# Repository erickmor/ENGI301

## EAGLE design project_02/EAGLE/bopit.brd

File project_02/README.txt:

# --------------------------------------------------------------------------
# Bop It Project PCB
# --------------------------------------------------------------------------
# License:   
Copyright 2021 Erick Morales

Redistribution and use in source and binary forms, with or without 
modification, are permitted provided that the following conditions are met:
 
1. Redistributions of source code must retain the above copyright notice, this 
list of conditions and the following disclaimer.
 
2. Redistributions in binary form must reproduce the above copyright notice, 
this list of conditions and the following disclaimer in the documentation 
and/or other materials provided with the distribution.

3. Neither the name of the copyright holder nor the names of its contributors 
may be used to endorse or promote products derived from this software without 
specific prior written permission.
 
THIS SOFTWARE IS PROVIDED BY THE COPYRIGHT HOLDERS AND CONTRIBUTORS "AS IS" 
AND ANY EXPRESS OR IMPLIED WARRANTIES, INCLUDING, BUT NOT LIMITED TO, THE 
IMPLIED WARRANTIES OF MERCHANTABILITY AND FITNESS FOR A PARTICULAR PURPOSE ARE 
DISCLAIMED. IN NO EVENT SHALL THE COPYRIGHT HOLDER OR CONTRIBUTORS BE LIABLE 
FOR ANY DIRECT, INDIRECT, INCIDENTAL, SPECIAL, EXEMPLARY, OR CONSEQUENTIAL 
DAMAGES (INCLUDING, BUT NOT LIMITED TO, PROCUREMENT OF SUBSTITUTE GOODS OR 
SERVICES; LOSS OF USE, DATA, OR PROFITS; OR BUSINESS INTERRUPTION) HOWEVER 
CAUSED AND ON ANY THEORY OF LIABILITY, WHETHER IN CONTRACT, STRICT LIABILITY, 
OR TORT (INCLUDING NEGLIGENCE OR OTHERWISE) ARISING IN ANY WAY OUT OF THE USE 
OF THIS SOFTWARE, EVEN IF ADVISED OF THE POSSIBILITY OF SUCH DAMAGE.
--------------------------------------------------------------------------

Hello!

This is a homemade version of Bop It along with its PCB design and gbr files. 
gbr files can be opened using gerbv software. 
To manufacture, site that was referenced was macrofab. 
Software used to develop PCB Design was EAGLE.
Most components were provided by Erik Welsh.
LCD Display was downloaded from this Github Repository.
 - https://github.com/eez-open/eagle-libraries
Joystick and PocketBeagle symbol components was created by me.  
Folder includes Library used, Schematics, and Layout.
Manufacturing folder with all gbr files is also provided.
Bill of Materials is also included.
 
Please reference Hackster.io page (https://www.hackster.io/ejm9/pocketbeagle-bop-it-project-39caf6)
    for more information on this project.
Link to Guthub
    - https://github.com/erickmor/ENGI301

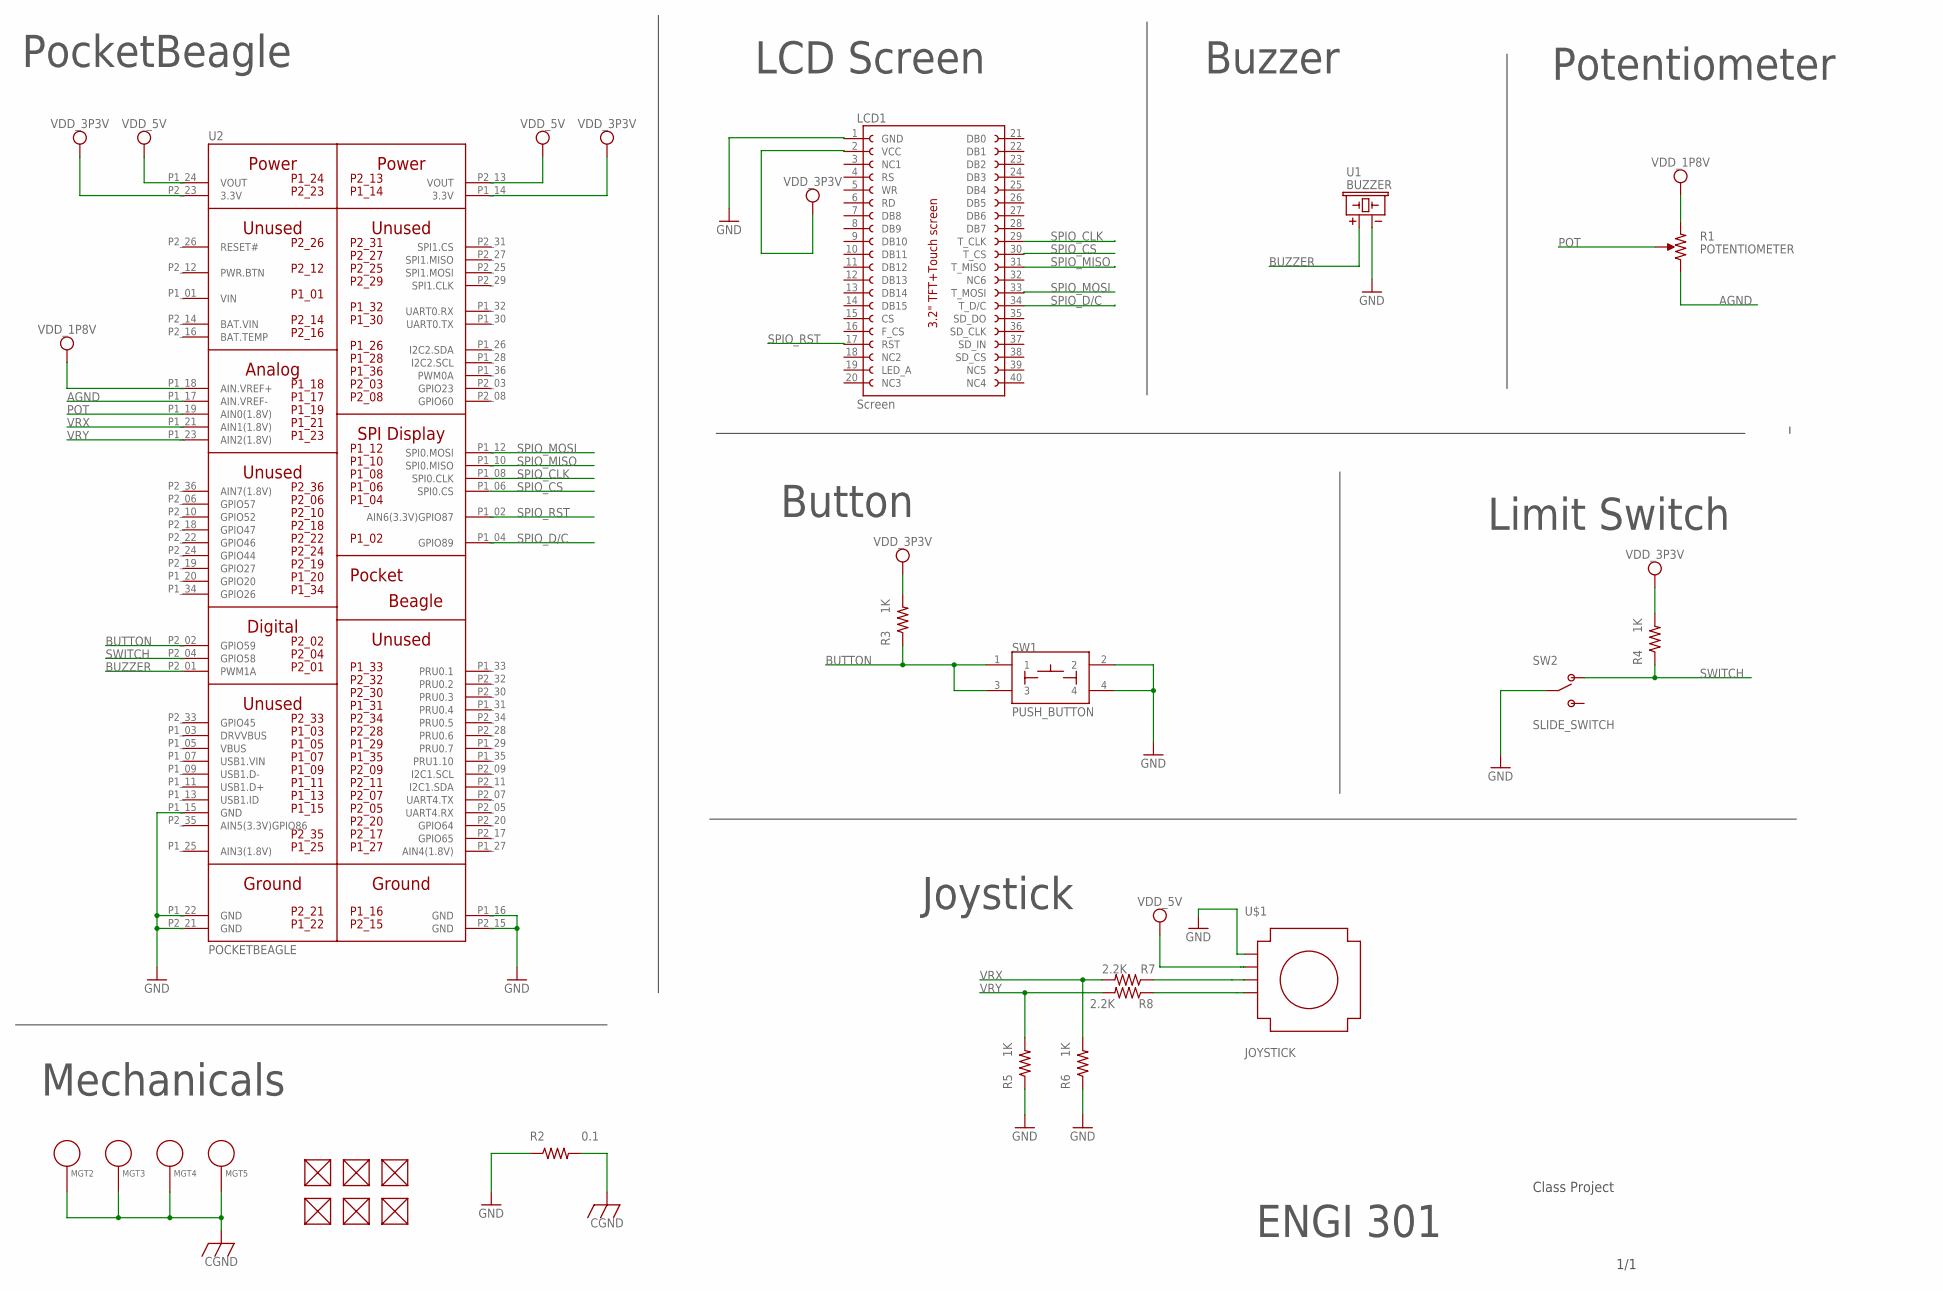
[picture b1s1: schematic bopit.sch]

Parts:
FUD1, FUD2, FUD3, FUD4, FUD5, FUD6: FIDUCIAL; FIDUCIAL_40MIL
LCD1: Screen; LCD_TFT_9341_MIRROR
MGT2, MGT3, MGT4, MGT5: MOUNTING_HOLE
R1: POTENTIOMETER; POT-PO90S
R2: 0.1; R0603
R3, R4, R5, R6: 1K; R0603
R7, R8: 2.2K; R0603
SW1: PUSH_BUTTON; BUTTON_12.5MM
SW2: SLIDE_SWITCH; JS202011SCQN
U1: BUZZER; BUZZER_6.5MM
U2: POCKETBEAGLE
U$1: JOYSTICK; EIA-JSTK

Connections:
AGND: R1.CCW, U2.P1_17 (AIN.VREF-)
BAT.VIN: U2.P2_14 (BAT.VIN)
BUTTON: R3.1, SW1.1, SW1.3, U2.P2_02 (GPIO59)
BUZZER: U1.+, U2.P2_01 (PWM1A)
CGND: MGT2.P$1, MGT3.P$1, MGT4.P$1, MGT5.P$1, R2.2
GND: LCD1.1 (GND), R2.1, R5.1, R6.1, SW1.2, SW1.4, SW2.2 (COMM), SW2.5 (COMM), U1.-, U2.P1_15 (GND), U2.P1_16 (GND), U2.P1_22 (GND), U2.P2_15 (GND), U2.P2_21 (GND), U$1.2 (GND)
unnamed: R7.1, U$1.3 (VRX)
unnamed: R8.1, U$1.4 (VRY)
POT: R1.S, U2.P1_19 (AIN0(1.8V))
SPIO_CLK: LCD1.29 (T_CLK), U2.P1_08 (SPI0.CLK)
SPIO_CS: LCD1.30 (T_CS), U2.P1_06 (SPI0.CS)
SPIO_D/C: LCD1.34 (T_D/C), U2.P1_04 (GPIO89)
SPIO_MISO: LCD1.31 (T_MISO), U2.P1_10 (SPI0.MISO)
SPIO_MOSI: LCD1.33 (T_MOSI), U2.P1_12 (SPI0.MOSI)
SPIO_RST: LCD1.17 (RST), U2.P1_02 (AIN6(3.3V)GPIO87)
SWITCH: R4.1, SW2.1 (POS1), SW2.4 (POS1), U2.P2_04 (GPIO58)
VDD_1P8V: R1.CW, U2.P1_18 (AIN.VREF+)
VDD_3P3V: LCD1.2 (VCC), R3.2, R4.2, U2.P1_14 (3.3V), U2.P2_23 (3.3V)
VDD_5V: U2.P1_24 (VOUT), U2.P2_13 (VOUT), U$1.1 (5V)
VIN: U2.P1_01 (VIN)
VRX: R6.2, R7.2, U2.P1_21 (AIN1(1.8V))
VRY: R5.2, R8.2, U2.P1_23 (AIN2(1.8V))

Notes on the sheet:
PocketBeagle
LCD Screen
Buzzer
Potentiometer
Button
Limit Switch
Joystick
Mechanicals
ENGI 301
Class Project
1/1

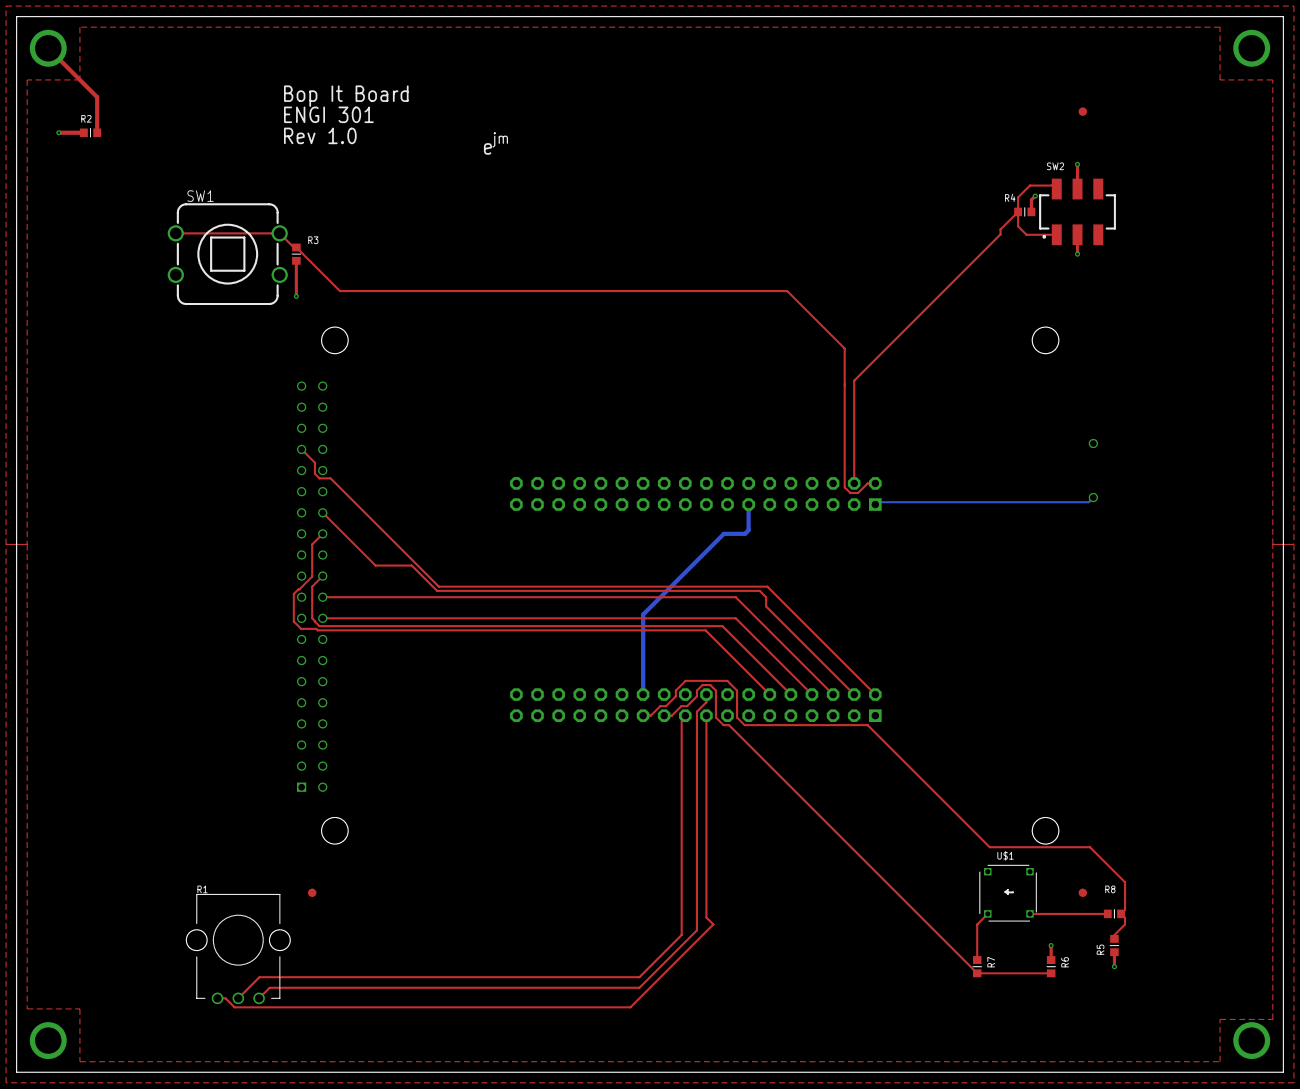
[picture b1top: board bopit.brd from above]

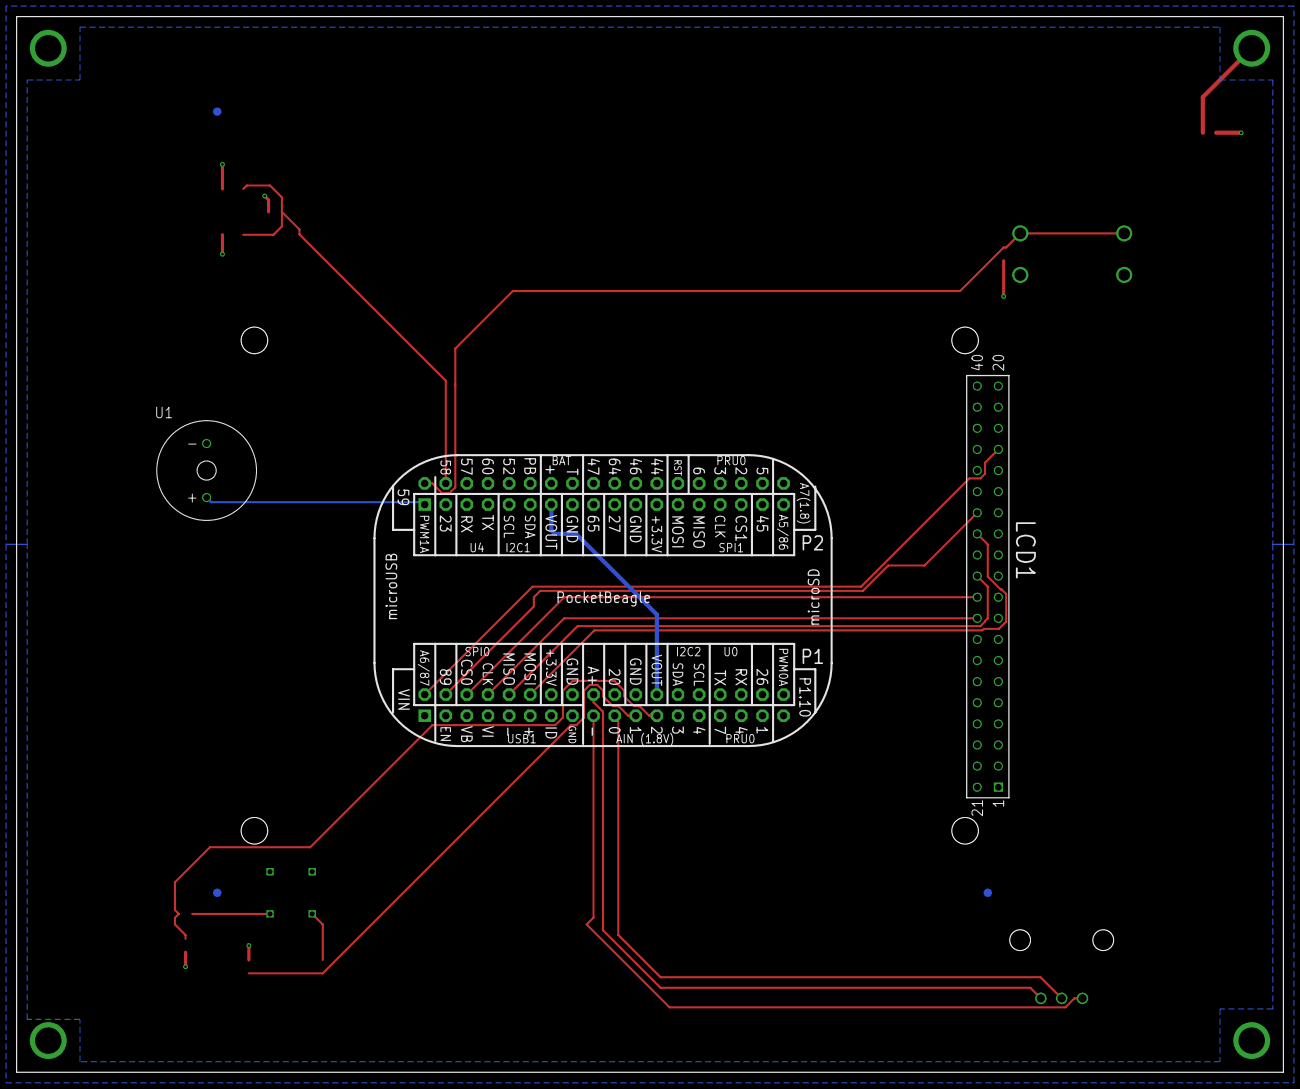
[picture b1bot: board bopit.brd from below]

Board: 4 copper layers, 152.4 x 127.0 mm, 24 parts (5 on the bottom side), 20 nets.

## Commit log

2021-09-16 Updating README.md
2021-10-05 finished simple cal file
2021-10-05 finished led blink file
2021-10-14 project proposal slides
2021-11-07 Fairly solidified code for project
2021-11-07 Code used to test hardware connections and worked
2021-11-07 image file used for button on display
2021-11-07 image file used for temporary game logo on display
2021-11-07 image file used for joystick on display
2021-11-07 image file used for limit switch on display
2021-11-07 image file used for potentiometer on display
2021-11-07 updated old image file
2021-11-08 SPI Library by Erik Welsh
2021-11-08 Code to configure pins at startup
2021-11-08 Run script for project
2021-11-08 Instructions and Building
2021-11-08 Log File for Cron
2021-11-08 Intro Image
2021-11-08 Final Push
2021-11-08 SPI Display Library by Erik Welsh - Adapted to always place text in center
2021-11-09 Updated Project Proposal
2021-11-09 Updated Project Code
2021-11-09 Updated hardware testing
2021-12-14 prject files
2021-12-14 project EAGLE files
2021-12-14 pcb manufacturing files
2021-12-14 project description
2021-12-15 Bill of Materials from EAGLE
